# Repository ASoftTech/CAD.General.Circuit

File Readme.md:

# General Circuit Schematics

## Overview

This is a collection of docs for the creation of PCB's via KiCad, as well as some schematic templates for projects. <br>
Also I've put some details here on using a LaserCutter (Manchester Hackspace one) <br>
As well as a CNC (Shapeoko2 / Ooznest OX) for making prototype PCB boards

  * Step by Step using KiCad to create a PCB
  * Using FlatCAM to create svg's for importing into Visicut
  * Step by Step using Visicut / The Manchester Hackspace Orange Laser Cutter to create PCB's
  * Using FlatCAM to create G-Code for importing into Chillipepr
  * Step by Step using Chillipepr to mill a PCB

## Cloning

To clone this repo

Method 1
```
git clone https://github.com/Hecatron-Machines/Hecatron.Kicad.General.git
git submodule init
git submodule update
```

Method 2
```
git clone --recursive https://github.com/Hecatron-Machines/Hecatron.Kicad.General.git
```

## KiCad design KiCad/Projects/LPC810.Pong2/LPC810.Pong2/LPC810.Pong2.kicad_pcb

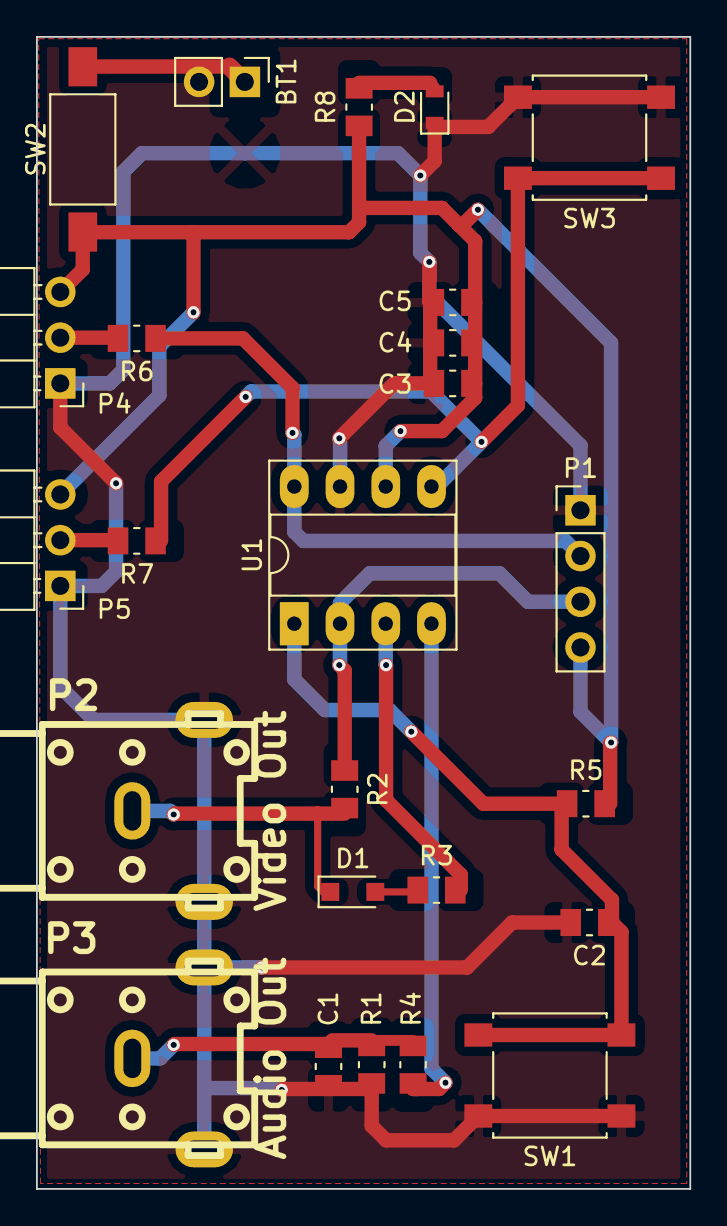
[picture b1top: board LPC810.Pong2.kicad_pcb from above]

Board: 2 copper layers, 36.3 x 64.0 mm, 25 parts (0 on the bottom side), 15 nets.

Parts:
BT1: Battery; PinHeader_1x02_P2.54mm_Vertical
C1: 2.2n; C_0805_2012Metric_Pad1.15x1.50mm_HandSolder
C2, C3, C4, C5: 100n; C_0805_2012Metric_Pad1.15x1.50mm_HandSolder
D1: BAS70JFILM; D_SOD-323_HandSoldering
D2: Power LED; LED_0603_1608Metric_Pad0.67x1.00mm_HandSolder
P1: Serial Prog; PinHeader_1x04_P2.54mm_Vertical
P2: Video Out; rca_yellow
P3: Audio Out; rca_yellow
P4: Paddle 1; PinHeader_1x03_P2.54mm_Horizontal
P5: Paddle 2; PinHeader_1x03_P2.54mm_Horizontal
R1: 620R; R_0805_2012Metric_Pad1.15x1.50mm_HandSolder
R2: 680R; R_0805_2012Metric_Pad1.15x1.50mm_HandSolder
R3, R8: 120R; R_0805_2012Metric_Pad1.15x1.50mm_HandSolder
R4, R5: 10K; R_0805_2012Metric_Pad1.15x1.50mm_HandSolder
R6, R7: 1K; R_0805_2012Metric_Pad1.15x1.50mm_HandSolder
SW1: ~Reset; SW_SPST_B3S-1000
SW2: Power; SW_SPST_FSMSM
SW3: Program; SW_SPST_B3S-1000
U1: LPC810M021FN8; DIP-8_W7.62mm_Socket_LongPads

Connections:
/DAUDIO: R4.1, U1.4
/DSYNC: P1.3, R2.1, U1.2
/DVIDEO: R3.1, U1.3
/P1: P1.2, R6.1, U1.8
/P2: R7.1, SW3.1, U1.5
GND: BT1.2, C1.2, C2.2, C3.2, C4.2, C5.2, D2.1, P1.1, P2.2, P3.2, P4.1, P5.1, R1.1, SW1.1, SW3.2, U1.7
unnamed: BT1.1, SW2.2
unnamed: C1.1, P3.1, R1.2, R4.2
unnamed: C2.1, R5.1, SW1.2, U1.1
unnamed: D1.1, P2.1, R2.2
unnamed: D1.2, R3.2
unnamed: D2.2, R8.2
unnamed: P4.2, R6.2
unnamed: P5.2, R7.2
VDD: C3.1, C4.1, C5.1, P1.4, P4.3, P5.3, R5.2, R8.1, SW2.1, U1.6

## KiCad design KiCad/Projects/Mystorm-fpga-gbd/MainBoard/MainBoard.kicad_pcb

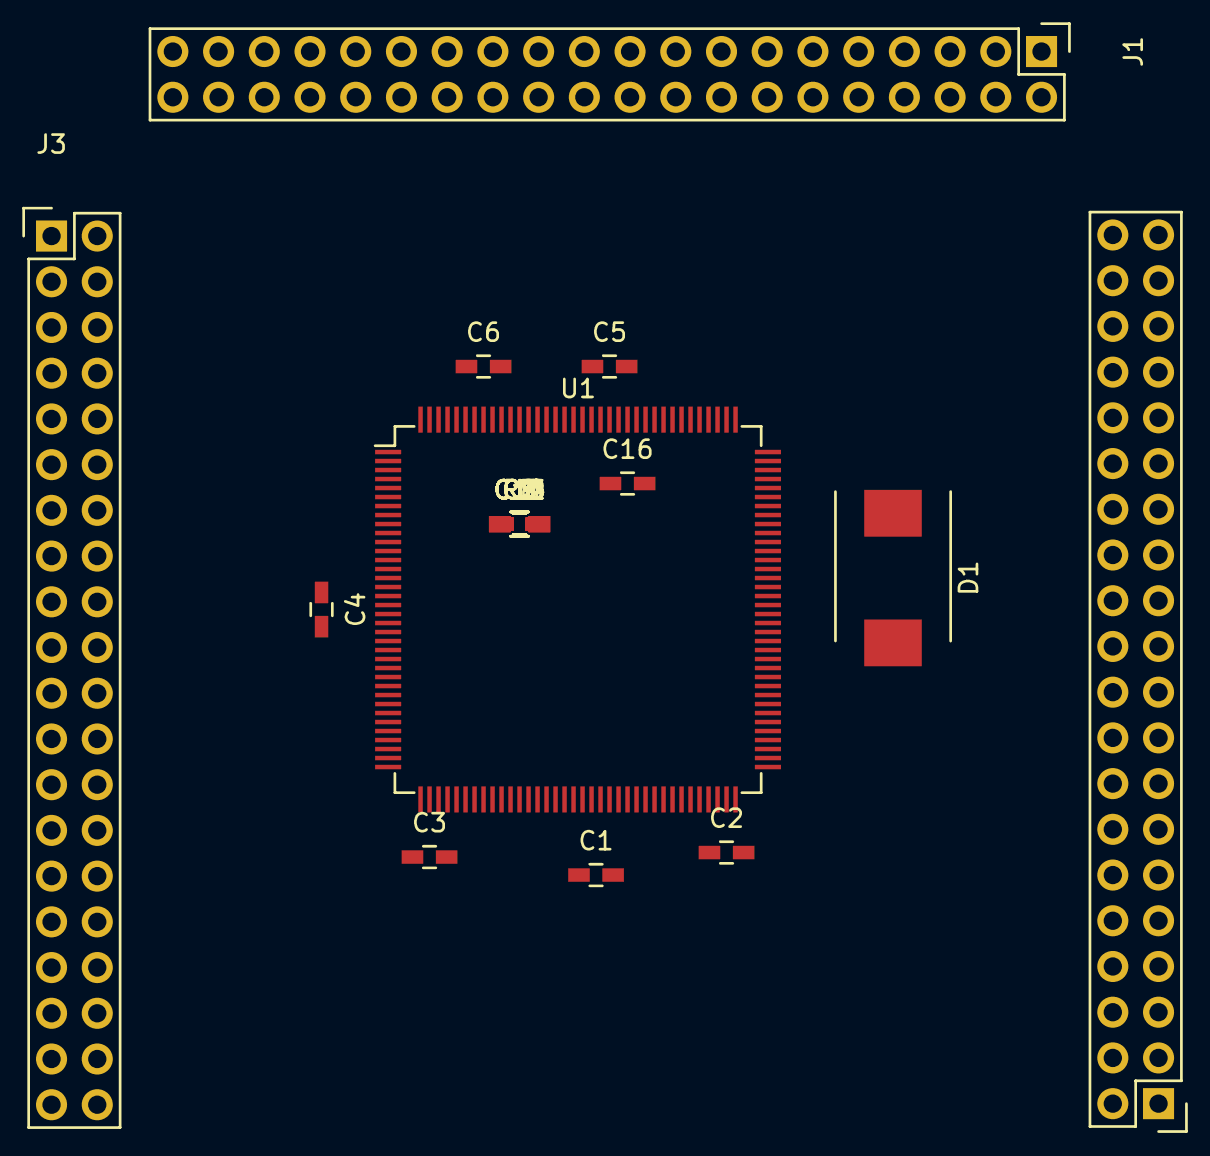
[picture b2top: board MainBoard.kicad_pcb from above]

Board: 2 copper layers, 24 parts (0 on the bottom side), 110 nets, no tracks yet.

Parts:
C1, C2, C3, C4, C5, C6, C7, C8, C9, C10, C11, C12, C13, C14, C15, C16: C_Small; C_0603_HandSoldering
D1: BAS70J; DO-214AB
J1, J2, J3: CONN_02X20; Pin_Header_Straight_2x20
R1, R2, R3: R_Small; R_0603_HandSoldering
U1: ICE40HX4K-144; TQFP-144_20x20mm_Pitch0.5mm

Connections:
+3V3: C2.2, C8.1, C9.1, C10.1, C11.1, C12.1, C13.1, C14.1, C15.1, C16.2, D1.2, J1.1, J2.1, J3.1, U1.6, U1.30, U1.46, U1.57, U1.72, U1.89, U1.100, U1.123, U1.131
+5V: J1.2, J2.2, J3.2
/Connectors/IO0_168: J1.14, U1.110
/Connectors/IO0_169: J1.13, U1.112
/Connectors/IO0_170: J1.16, U1.113
/Connectors/IO0_171: J1.15, U1.114
/Connectors/IO0_172: J1.18, U1.115
/Connectors/IO0_173: J1.17, U1.116
/Connectors/IO0_174: J1.20, U1.117
/Connectors/IO0_177: J1.19, U1.118
/Connectors/IO0_178: J1.22, U1.119
/Connectors/IO0_179: J1.21, U1.120
/Connectors/IO0_181: J1.24, U1.121
/Connectors/IO0_190: J1.23, U1.122
/Connectors/IO0_191: J1.26, U1.124
/Connectors/IO0_192: J1.25, U1.125
/Connectors/IO0_197: J1.28, U1.128
/Connectors/IO0_206: J1.27, U1.130
/Connectors/IO0_212: J1.30, U1.134
/Connectors/IO0_213: J1.29, U1.135
/Connectors/IO0_214: J1.32, U1.136
/Connectors/IO0_215: J1.31, U1.137
/Connectors/IO0_216: J1.34, U1.138
/Connectors/IO0_217: J1.33, U1.139
/Connectors/IO0_219: J1.36, U1.141
/Connectors/IO0_220: J1.35, U1.142
/Connectors/IO0_221: J1.38, U1.143
/Connectors/IO0_222: J1.37, U1.144
/Connectors/IO1_109: J2.19, U1.73
/Connectors/IO1_110: J2.22, U1.74
/Connectors/IO1_111: J2.21, U1.75
/Connectors/IO1_112: J2.24, U1.76
/Connectors/IO1_114: J2.23, U1.78
/Connectors/IO1_115: J2.26, U1.79
/Connectors/IO1_116: J2.25, U1.80
/Connectors/IO1_117: J2.28, U1.81
/Connectors/IO1_118: J2.27, U1.82
/Connectors/IO1_119: J2.30, U1.83
/Connectors/IO1_120: J2.29, U1.84
/Connectors/IO1_128: J2.32, U1.85
/Connectors/IO1_136: J2.31, U1.87
/Connectors/IO1_137: J2.34, U1.88
/Connectors/IO1_138: J2.33, U1.90
/Connectors/IO1_139: J2.36, U1.91
/Connectors/IO1_140: J2.35, U1.93
/Connectors/IO1_141: J2.38, U1.94
/Connectors/IO1_144: J2.37, U1.95
/Connectors/IO1_146: J1.4, U1.96
/Connectors/IO1_147: J1.3, U1.97
/Connectors/IO1_148: J1.6, U1.98
/Connectors/IO1_152: J1.5, U1.99
/Connectors/IO1_160: J1.8, U1.101
/Connectors/IO1_161: J1.7, U1.102
/Connectors/IO1_164: J1.10, U1.104
/Connectors/IO1_165: J1.9, U1.105
/Connectors/IO1_166: J1.12, U1.106
/Connectors/IO1_167: J1.11, U1.107
/Connectors/IO2_56: J3.31, U1.37
/Connectors/IO2_57: J3.32, U1.38
/Connectors/IO2_61: J3.33, U1.39
/Connectors/IO2_63: J3.34, U1.41
/Connectors/IO2_64: J3.35, U1.42
/Connectors/IO2_71: J3.36, U1.43
/Connectors/IO2_72: J3.37, U1.44
/Connectors/IO2_73: J3.38, U1.45
/Connectors/IO2_79: J2.10, U1.47
/Connectors/IO2_80: J2.9, U1.48
/Connectors/IO2_81: J2.12, U1.49
/Connectors/IO2_82: J2.11, U1.52
/Connectors/IO2_91: J2.14, U1.55
/Connectors/IO2_94: J2.13, U1.56
/Connectors/IO2_95: J2.16, U1.60
/Connectors/IO2_96: J2.15, U1.61
/Connectors/IO2_102: J2.18, U1.62
/Connectors/IO2_103: J2.17, U1.63
/Connectors/IO2_104: J2.20, U1.64
/Connectors/IO3_21: J3.3, U1.1
/Connectors/IO3_22: J3.4, U1.2
/Connectors/IO3_31: J3.5, U1.3
/Connectors/IO3_32: J3.6, U1.4
/Connectors/IO3_41: J3.7, U1.7
/Connectors/IO3_42: J3.8, U1.8
/Connectors/IO3_51: J3.9, U1.9
/Connectors/IO3_52: J3.10, U1.10
/Connectors/IO3_81: J3.11, U1.11
/Connectors/IO3_82: J3.12, U1.12
/Connectors/IO3_101: J3.13, U1.15
/Connectors/IO3_102: J3.14, U1.16
/Connectors/IO3_121: J3.15, U1.17
/Connectors/IO3_122: J3.16, U1.18
/Connectors/IO3_131: J3.17, U1.19
/Connectors/IO3_132: J3.18, U1.20
/Connectors/IO3_141: J3.19, U1.21
/Connectors/IO3_142: J3.20, U1.22
/Connectors/IO3_171: J3.21, U1.23
/Connectors/IO3_172: J3.22, U1.24
/Connectors/IO3_181: J3.23, U1.25
/Connectors/IO3_182: J3.24, U1.26
/Connectors/IO3_231: J3.25, U1.28
/Connectors/IO3_232: J3.26, U1.29
/Connectors/IO3_241: J3.27, U1.31
/Connectors/IO3_242: J3.28, U1.32
/Connectors/IO3_251: J3.29, U1.33
/Connectors/IO3_252: J3.30, U1.34
/FPGA/~SS: R1.2, U1.71
GND: C1.2, C2.1, C3.1, C4.1, C5.1, C6.1, C7.2, C8.2, C9.2, C10.2, C11.2, C12.2, C13.2, C14.2, C15.2, C16.1, J1.39, J1.40, J2.39, J2.40, J3.39, J3.40, U1.5, U1.13, U1.14, U1.53, U1.59, U1.69, U1.103, U1.127, U1.132, U1.140
unnamed: C1.1, R1.1, R2.2, U1.54
unnamed: C7.1, R3.2, U1.126
unnamed: D1.1, U1.108
VCC: C3.2, C4.2, C5.2, C6.2, R2.1, R3.1, U1.27, U1.40, U1.92, U1.111

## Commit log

2017-02-25 Deployed c8d1556 with MkDocs version: 0.16.1
2019-12-22 doc update
